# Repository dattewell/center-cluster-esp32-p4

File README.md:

## Issues/bug fixes

### Older boards/revision errors

This board is P4 v1.3, builds require SELECTS_REV_LESS_V3=y.

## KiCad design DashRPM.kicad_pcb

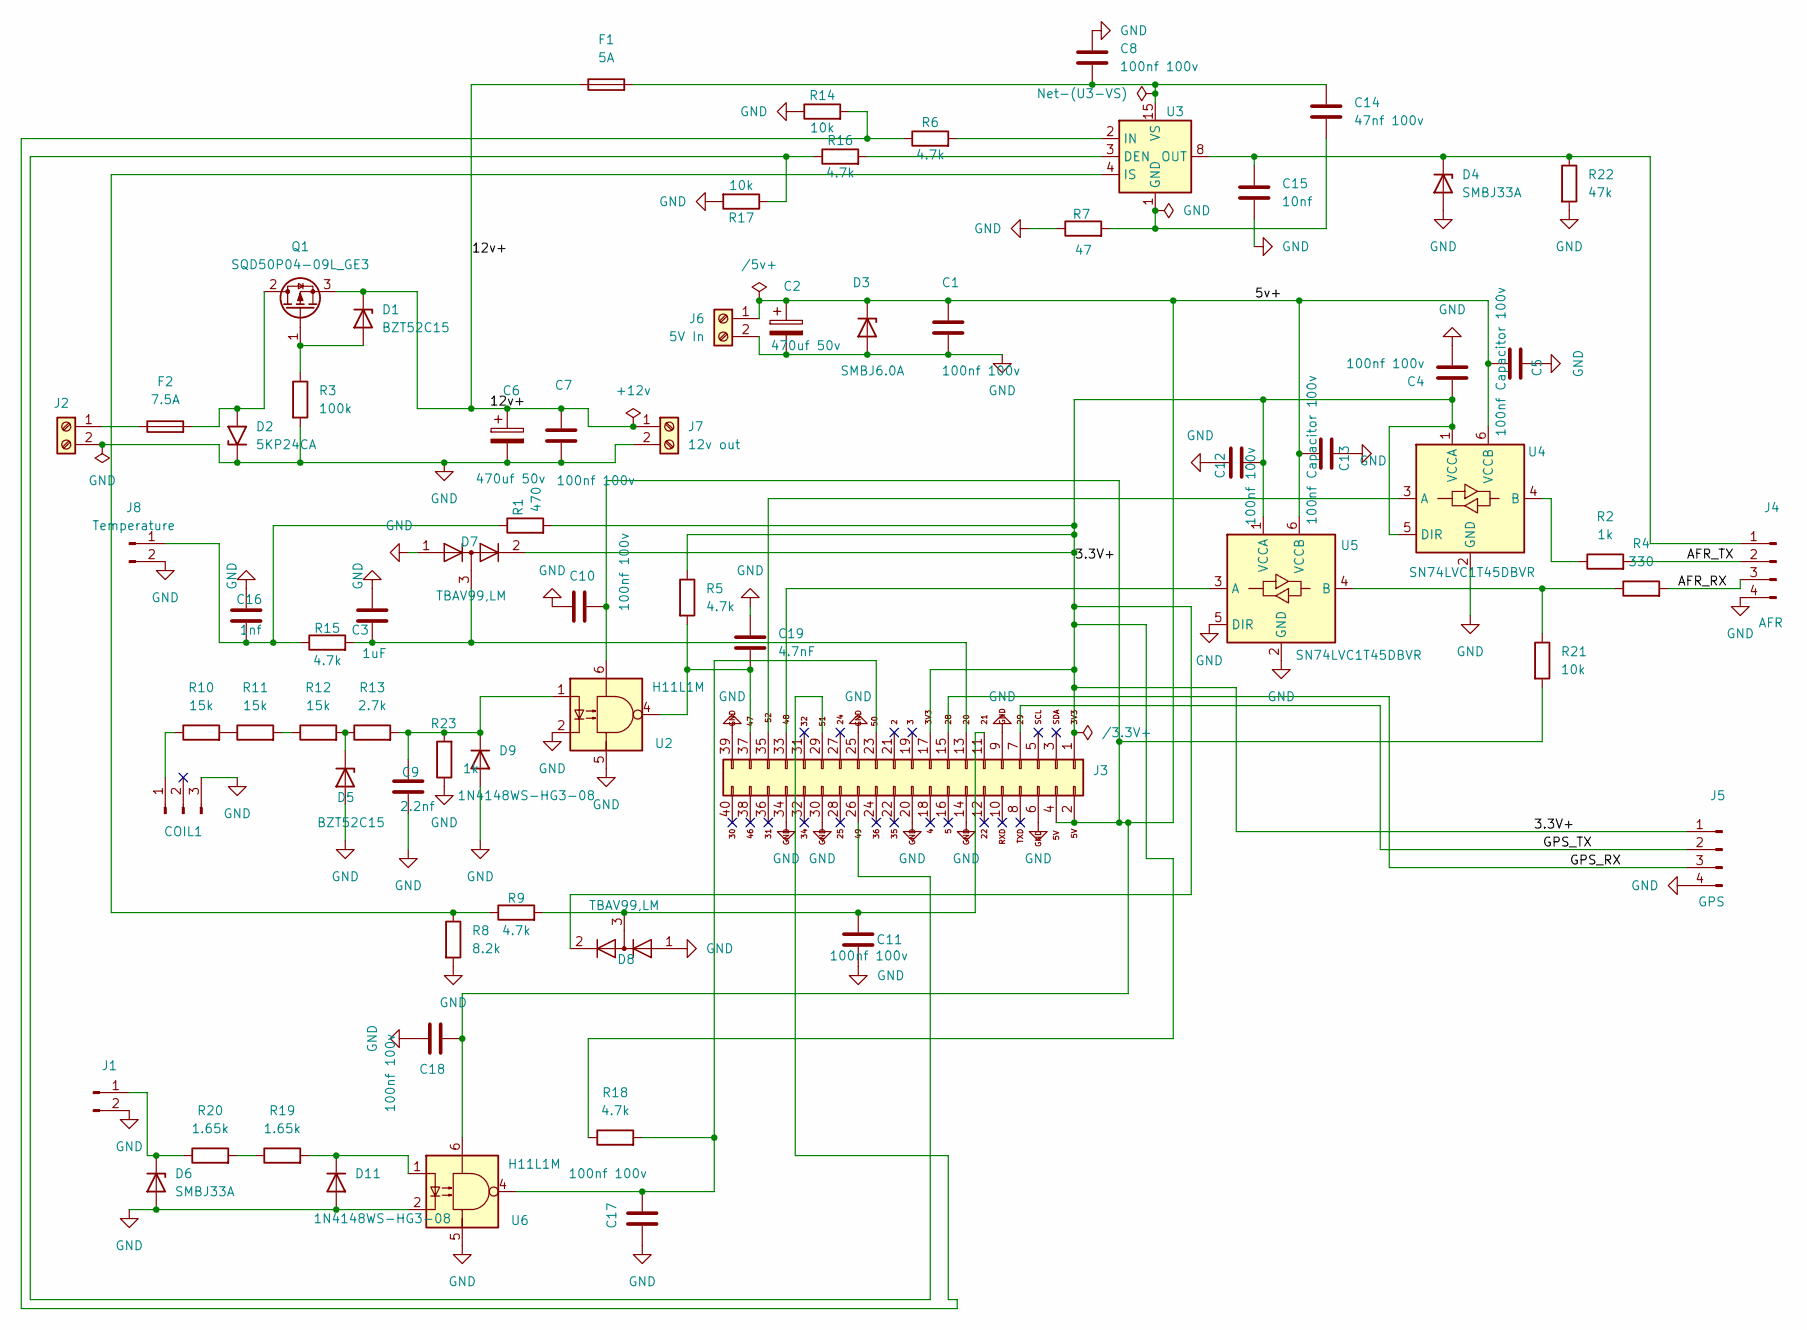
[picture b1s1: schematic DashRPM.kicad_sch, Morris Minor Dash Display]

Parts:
C1, C4, C5, C7, C8, C10, C11, C12, C13, C17, C18: 100nf 100v; C_0805_2012Metric; LCSC C28233
C2, C6: 470uf 50v; CP_Radial_D10.0mm_P5.00mm; LCSC C713167
C3: 1uF; C_0805_2012Metric; LCSC C28323
C9: 2.2nf; C_0805_2012Metric; LCSC C1728
C14: 47nf 100v; C_0805_2012Metric; LCSC C161267
C15: 10nf; C_0805_2012Metric; LCSC C161265
C16: 1nf; C_0805_2012Metric; LCSC C46653
C19: 4.7nF; C_0805_2012Metric; LCSC C415370
COIL1: Coil; JST_XH_B3B-XH-A_1x03_P2.50mm_Vertical; LCSC C144394
D1, D5: BZT52C15; D_SOD-123; LCSC C27754
D2: 5KP24CA; D_5KP_P12.70mm_Horizontal; LCSC C3704111
D3: SMBJ6.0A; D_SMB; LCSC C83270
D4, D6: SMBJ33A; D_SMB_Handsoldering; LCSC C224019
D7, D8: TBAV99,LM; SOT-23; LCSC C145146
D9, D11: 1N4148WS-HG3-08; D_SOD-323_HandSoldering; LCSC C3313072
F1: 5A; Fuseholder_Blade_Mini_Keystone_3568; LCSC C5249699
F2: 7.5A; Fuseholder_Blade_Mini_Keystone_3568; LCSC C5249699
J1: Headlight; JST_XH_B2B-XH-A_1x02_P2.50mm_Vertical; LCSC C158012
J2: 12v In; TerminalBlock_MaiXu_MX126-5.0-02P_1x02_P5.00mm; LCSC C3820334
J3: To Display; IDC-Header_2x20_P2.54mm_Vertical; LCSC C9138
J4: AFR; JST_VH_B4P-VH_1x04_P3.96mm_Vertical; LCSC C160317
J5: GPS; JST_XH_B4B-XH-A_1x04_P2.50mm_Vertical; LCSC C144395
J6: 5V In; TerminalBlock_MaiXu_MX126-5.0-02P_1x02_P5.00mm; LCSC C3820334
J7: 12v out; TerminalBlock_MaiXu_MX126-5.0-02P_1x02_P5.00mm; LCSC C3820334
J8: Temperature; JST_XH_B2B-XH-A_1x02_P2.50mm_Vertical; LCSC C158012
Q1: SQD50P04-09L_GE3; TO-252-3_TabPin2; LCSC C5160151
R1: 470; R_0805_2012Metric_Pad1.20x1.40mm_HandSolder; LCSC C491182
R2, R23: 1k; R_0805_2012Metric_Pad1.20x1.40mm_HandSolder; LCSC C191555
R3: 100k; R_0805_2012Metric_Pad1.20x1.40mm_HandSolder; LCSC C191554
R4: 330; R_0805_2012Metric_Pad1.20x1.40mm_HandSolder; LCSC C2479687
R5, R6, R9, R15, R16, R18: 4.7k; R_0805_2012Metric_Pad1.20x1.40mm_HandSolder; LCSC C473295
R7: 47; R_0805_2012Metric_Pad1.20x1.40mm_HandSolder; LCSC C490799
R8: 8.2k; R_0805_2012Metric_Pad1.20x1.40mm_HandSolder; LCSC C445657
R10, R11, R12: 15k; R_2512_6332Metric_Pad1.40x3.35mm_HandSolder; LCSC C965951
R13: 2.7k; R_0805_2012Metric_Pad1.20x1.40mm_HandSolder; LCSC C409999
R14, R17: 10k; R_1206_3216Metric_Pad1.30x1.75mm_HandSolder; LCSC C6492313
R19, R20: 1.65k; R_1206_3216Metric_Pad1.30x1.75mm_HandSolder; LCSC C2482762
R21: 10k; R_0805_2012Metric_Pad1.20x1.40mm_HandSolder; LCSC C191101
R22: 47k; R_0805_2012Metric_Pad1.20x1.40mm_HandSolder; LCSC C441957
U2, U6: H11L1M; SMDIP-6_W7.62mm; LCSC C16587
U3: BTS7004-1EPP; Infineon_PG-TSDSO-14-22; LCSC C534825
U4, U5: SN74LVC1T45DBVR; SOT-23-6; LCSC C7843

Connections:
/3.3V+: C4.1, C12.1, D7.2 (A), D8.2 (A), J3.1 (3V3), J3.17 (3V3), J5.1, R1.2, R5.1, R18.1, U4.1 (VCCA), U4.5 (DIR), U5.1 (VCCA)
/5v+: C1.1, C2.1, C5.2, C10.2, C13.2, C18.1, D3.1 (K), J3.2 (5V), J3.4 (5V), J6.1, R21.2, U2.6, U4.6 (VCCB), U5.6 (VCCB), U6.6
/12v+: C6.1, C7.1, D1.1 (K), F1.1, J7.1, Q1.3 (S)
/AFR_RX: J4.3, R4.2
/AFR_TX: J4.2, R2.2
/GPS_RX: J3.15 (28), J5.3
/GPS_TX: J3.7 (29), J5.2
GND: C1.2, C2.2, C3.1, C4.2, C5.1, C6.2, C7.2, C8.1, C9.2, C10.1, C11.1, C12.2, C13.1, C15.2, C16.1, C17.1, C18.2, C19.1, COIL1.3, D2.1 (A1), D3.2 (A), D4.2 (A), D5.2 (A), D6.2 (A), D7.1 (K), D8.1 (K), D9.2 (A), D11.2 (A), J1.2, J2.2, J3.6 (GND), J3.9 (GND), J3.14 (GND), J3.20 (GND), J3.25 (GND), J3.30 (GND), J3.34 (GND), J3.39 (GND), J4.4, J5.4, J6.2, J7.2, J8.2, R3.2, R7.1, R8.2, R14.1, R17.2, R22.2, R23.1, U2.2, U2.5, U4.2 (GND), U5.2 (GND), U5.5 (DIR), U6.2, U6.5
unnamed: COIL1.1, R10.1
unnamed: D1.2 (A), Q1.1 (G), R3.1
unnamed: D2.2 (A2), F2.2, Q1.2 (D)
unnamed: C15.1, D4.1 (K), J4.1, R22.1, U3.8 (OUT), U3.9 (OUT), U3.10 (OUT), U3.12 (OUT), U3.13 (OUT), U3.14 (OUT)
unnamed: D5.1 (K), R12.2, R13.1
unnamed: D6.1 (K), J1.1, R20.1
unnamed: C9.1, D9.1 (K), R13.2, R23.2, U2.1
unnamed: D11.1 (K), R19.2, U6.1
unnamed: F2.1, J2.1
unnamed: C3.2, D7.3 (K), J3.13 (20), R15.2
unnamed: C11.2, D8.3 (K), J3.11 (21), R9.2
unnamed: C19.2, J3.37 (47), R5.2, U2.4
unnamed: J3.33 (48), U5.3 (A)
unnamed: J3.26 (49), R16.1, R17.1
unnamed: C17.2, J3.23 (50), R18.2, U6.4
unnamed: J3.29 (51), R6.1, R14.2
unnamed: J3.35 (52), U4.3 (A)
unnamed: C16.2, J8.1, R1.1, R15.1
unnamed: R10.2, R11.1
unnamed: R11.2, R12.1
unnamed: R19.1, R20.2
unnamed: R16.2, U3.3 (DEN)
unnamed: C14.2, R7.2, U3.1 (GND)
unnamed: R6.2, U3.2 (IN)
unnamed: R8.1, R9.1, U3.4 (IS)
unnamed: C8.2, C14.1, F1.2, U3.15 (VS)
unnamed: R2.1, U4.4 (B)
unnamed: R4.1, R21.1, U5.4 (B)

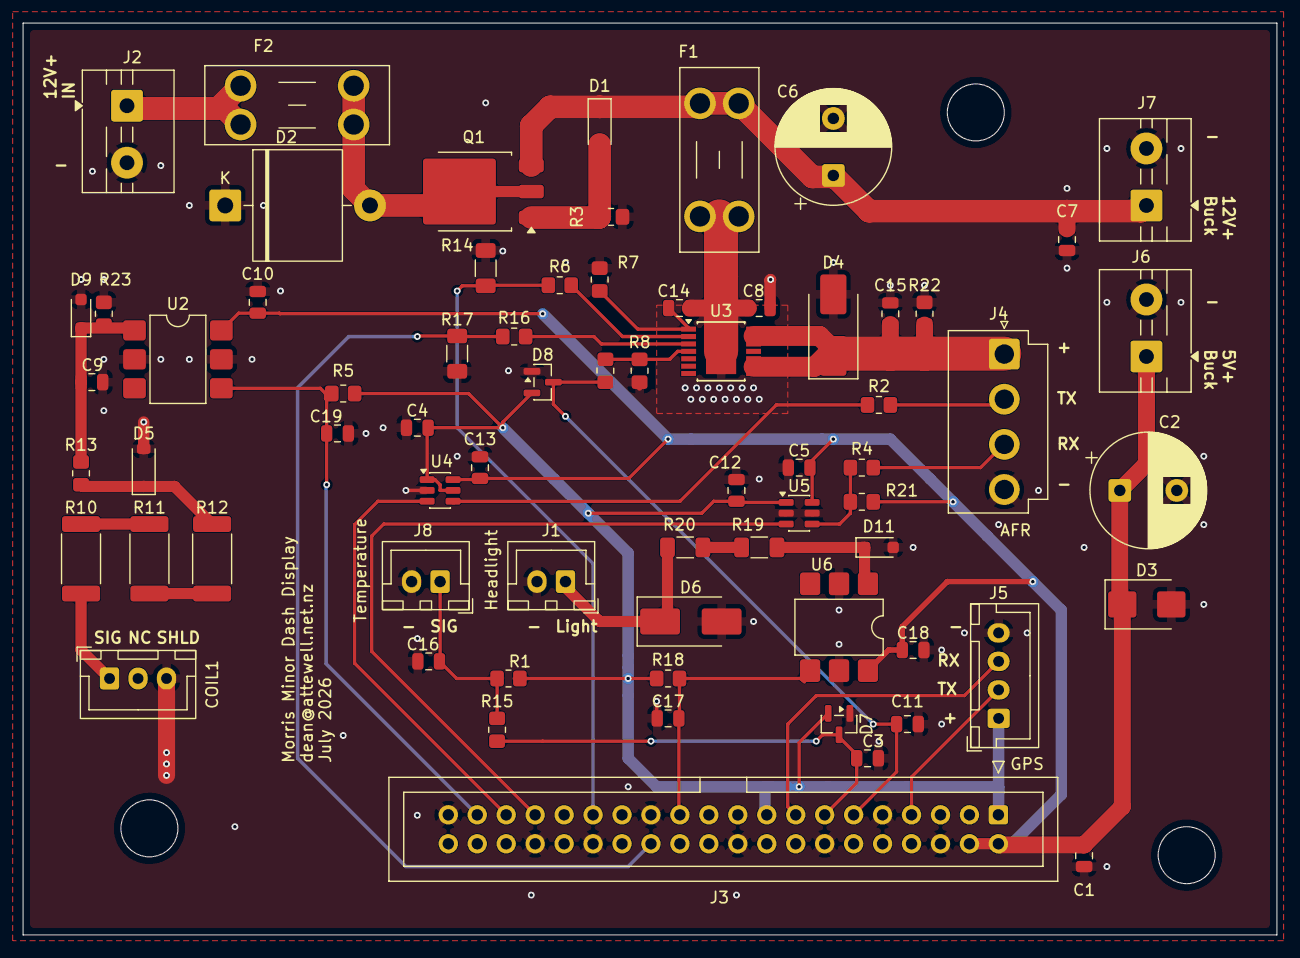
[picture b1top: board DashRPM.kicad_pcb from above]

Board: 2 copper layers, 110.0 x 80.0 mm, 69 parts (0 on the bottom side), 36 nets.

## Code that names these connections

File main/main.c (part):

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//------------------------------------------------//

//-------------GPS (u-blox M10)-------------//
// GPS RX/TX per netlist (/GPS_TX net = J3 pin 7 = GPIO29 = ESP RX;
// /GPS_RX net = J3 pin 15 = GPIO28 = ESP TX). Net names are from the
// module's perspective, so ESP_RX reads the net called GPS_TX and vice versa.
#define GPS_RX_PIN        29
#define GPS_UART_NUM      UART_NUM_3
#define GPS_TX_PIN        28
#define GPS_BAUD_RATE     38400
#define GPS_BUF_SIZE      1024
#define GPS_MIN_VALID_MPH 3.0f
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//-------------------------------------------------------------------------------------//

//-------------AFR UART (14point7 Spartan)-------------//
// TX/RX assignment per schematic: AFR_TX on U4 (GPIO52), AFR_RX on U5 (GPIO48).
#define AFR_UART_NUM   UART_NUM_1
#define AFR_TX_PIN     52
#define AFR_RX_PIN     48
#define AFR_BAUD_RATE  9600
//--------------------------------------------------------------------//

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
    xTaskCreatePinnedToCore(adc_task, "adc_task", 4096, NULL, 5, NULL, 0);

    uart_init(GPS_UART_NUM, GPS_TX_PIN, GPS_RX_PIN, (GPS_BUF_SIZE*2), GPS_BAUD_RATE);
    gps_ubx_query_chip_info(GPS_UART_NUM);
    xTaskCreatePinnedToCore(gps_task, "gps_task", 4096, NULL, 5, NULL, 0);

    uart_init(AFR_UART_NUM, AFR_TX_PIN, AFR_RX_PIN, 256, AFR_BAUD_RATE);
    xTaskCreatePinnedToCore(afr_task, "afr_task", 4096, NULL, 5, NULL, 0);
}

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
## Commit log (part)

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2026-04-02 fix: adding boost and afr to main gauge
2026-04-19 adding fuel comp
2026-06-02 feat: adding emtron can protocol
